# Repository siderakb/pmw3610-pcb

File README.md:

# PMW3610 PCB

Breakout board for the [PixArt PMW3610DM-SUDU](https://www.pixart.com/products-detail/21/PMW3610DM-SUDU), a low-power laser mouse sensor. An alternative to the [PMW3360 PCB](https://github.com/siderakb/pmw3360-pcb) for low-power applications. Can be used to make a mouse or trackball.

✨ Features:

- Compatible with [ZMK](https://zmk.dev/) projects. [Demo video](https://youtu.be/nyLZ6U8h7f0?t=17)
- Operates at either 1.8V or 3.3V voltage levels.
- Supports both 2.54mm pin headers and 0.5mm-pitch FFC/FPC connectors.
- The optical center of the sensor is located in the center of the PCB.

## PCB

Online preview available [here](https://kicanvas.org/?github=https%3A%2F%2Fgithub.com%2Fsiderakb%2Fpmw3610-pcb), powered by [KiCanvas](https://github.com/theacodes/kicanvas).

## Docs

📖 For more detailed information, please refer to the [docs](https://siderakb.ziteh.dev/mouse-sensors/pmw3610/rev2/) ([alternative link](https://github.com/siderakb/siderakb-website/blob/starlight/main/src/content/docs/mouse-sensors/pmw3610/rev2.md)).

[Changelog](./CHANGELOG.md)

## License

- **Hardware**: Available under the [CERN-OHL-P v2](/LICENSE) permissive license.
- **Firmware**: Licensed under [Apache 2.0](https://spdx.org/licenses/Apache-2.0.html) as identified by the SPDX in each file.

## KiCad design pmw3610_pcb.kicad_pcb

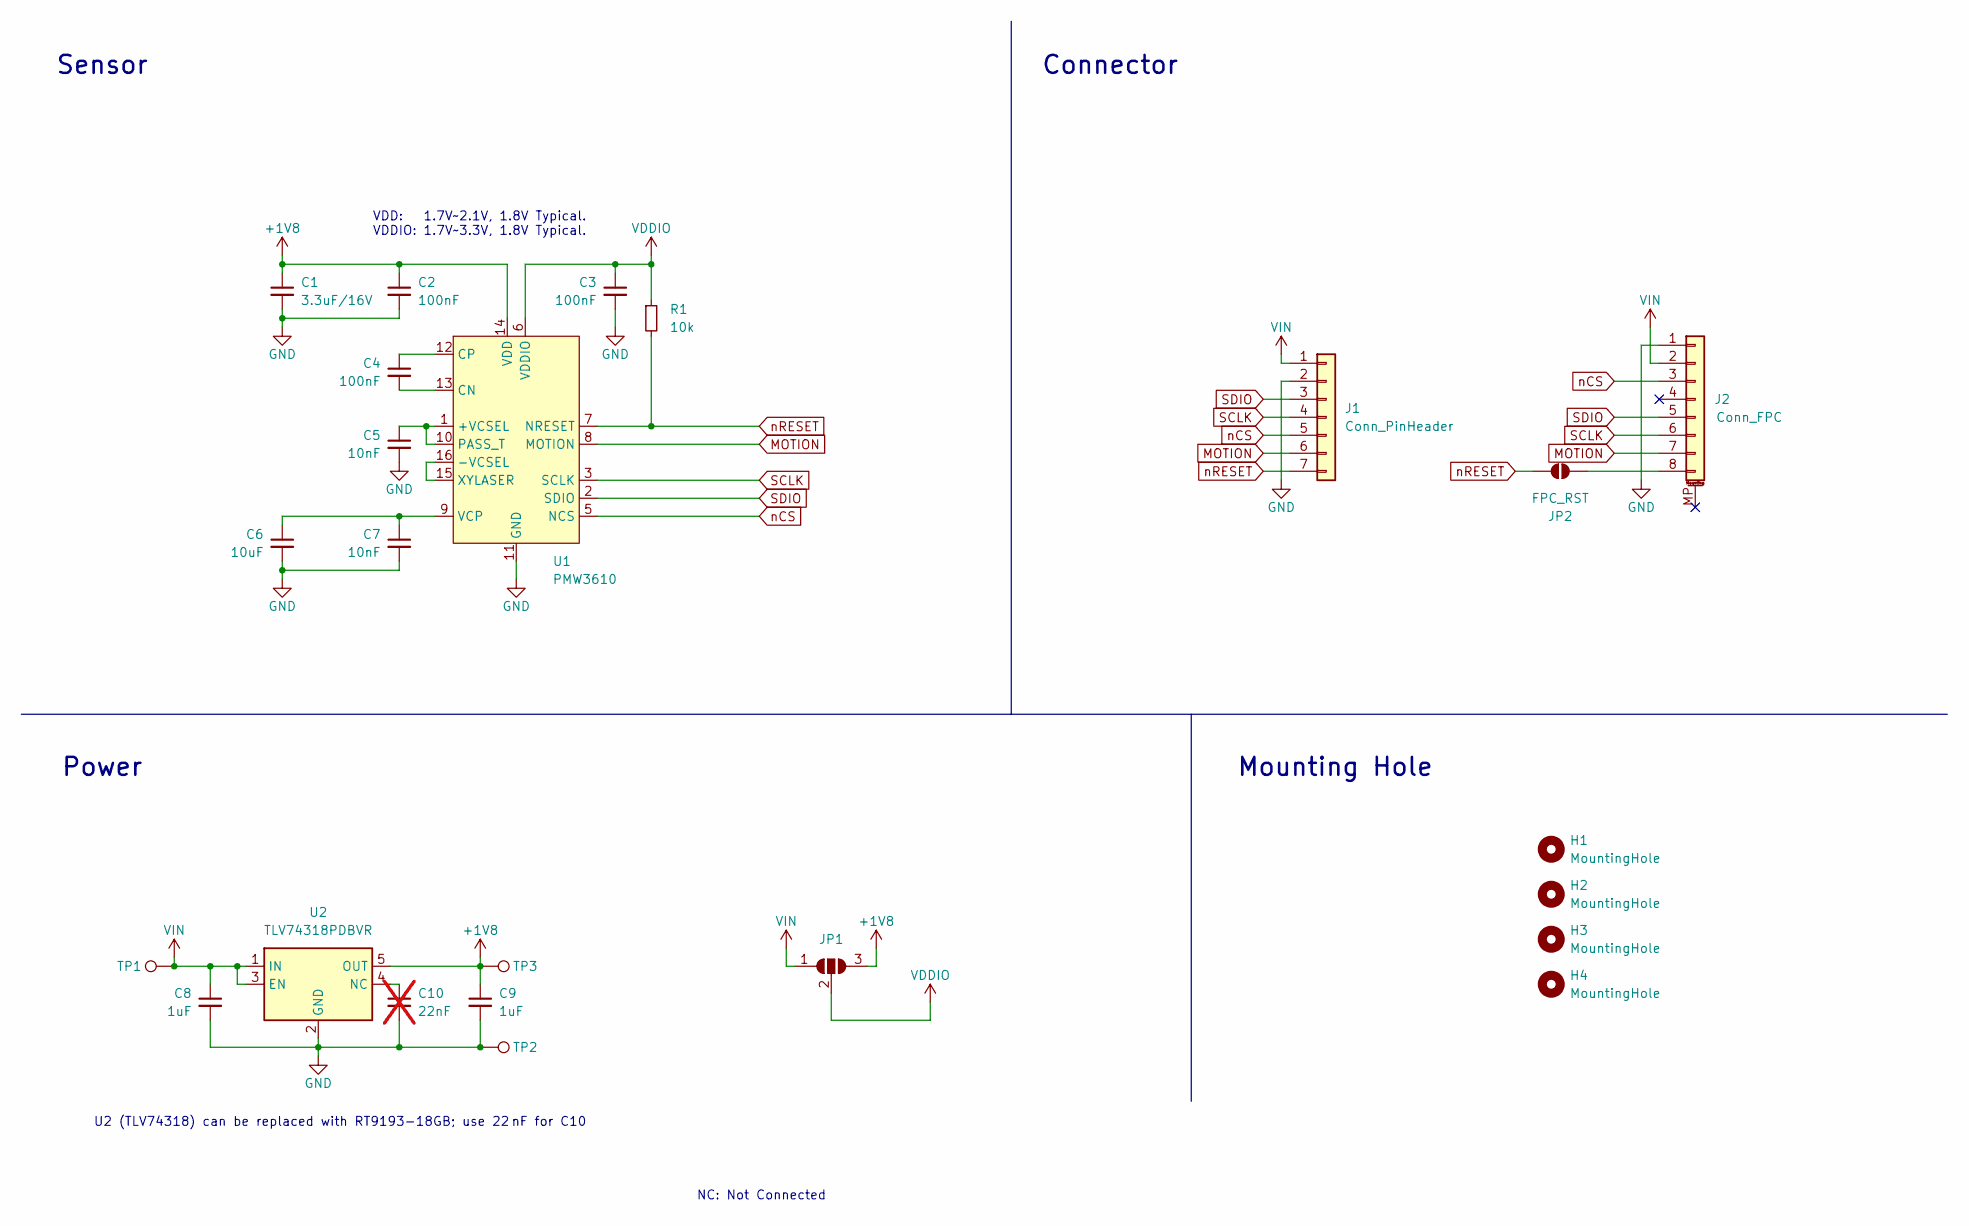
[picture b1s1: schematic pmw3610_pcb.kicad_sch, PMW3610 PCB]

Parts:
C1: 3.3uF/16V; C_0805_2012Metric; MFR. Part # TCC0805X7R335K250FT; JLCPCB Part # C7393948
C2, C3, C4: 100nF; C_0603_1608Metric; MFR. Part # CC0603KRX7R9BB104; JLCPCB Part # C14663
C5, C7: 10nF; C_0603_1608Metric; MFR. Part # 0603B103K500NT; JLCPCB Part # C57112
C6: 10uF; C_0805_2012Metric; MFR. Part # CL21A106KAYNNNE; JLCPCB Part # C15850
C8, C9: 1uF; C_0603_1608Metric; MFR. Part # CL10A105KB8NNNC; JLCPCB Part # C15849
C10: 22nF; C_0603_1608Metric; MFR. Part # CL10B223KB8NNNC; JLCPCB Part # C21122; not fitted
H1, H2, H3, H4: MountingHole; MountingHole_3.2mm_M3_ISO14580
J1: Conn_PinHeader; PinHeader_1x07_P2.54mm_Vertical
J2: Conn_FPC; FPC_8P_0.5mm_AFC01-S08FCA-00; MFR. Part # AFC01-S08FCA-00; JLCPCB Part # C262657
JP1: SolderJumper_3_Open; SolderJumper-3_P1.3mm_Open_RoundedPad1.0x1.5mm_NumberLabels
JP2: FPC_RST; SolderJumper-2_P1.3mm_Open_RoundedPad1.0x1.5mm
R1: 10k; R_0603_1608Metric; MFR. Part # 0603WAF1002T5E; JLCPCB Part # C25804
TP1, TP2, TP3: TestPoint; TestPoint_Pad_D1.5mm
U1: PMW3610; PMW3610DM-SUDU 16Pin; MFR. Part # PMW3610DM-SUDU; JLCPCB Part # C42442560
U2: TLV74318PDBVR; SOT-23-5_HandSoldering; MFR. Part # TLV74318PDBVR; JLCPCB Part # C485152

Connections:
+1V8: C1.1, C2.1, C9.1, JP1.3 (B), TP3.1, U1.14 (VDD), U2.5 (OUT)
GND: C1.2, C2.2, C3.2, C5.2, C6.2, C7.2, C8.2, C9.2, C10.2, J1.2, J2.1, TP2.1, U1.11 (GND), U2.2 (GND)
MOTION: J1.6, J2.7, U1.8 (MOTION)
unnamed: J2.8, JP2.2 (B)
unnamed: C5.1, U1.1 (+VCSEL), U1.10 (PASS_T)
unnamed: U1.15 (XYLASER), U1.16 (-VCSEL)
unnamed: C4.2, U1.13 (CN)
unnamed: C4.1, U1.12 (CP)
unnamed: C6.1, C7.1, U1.9 (VCP)
unnamed: C10.1, U2.4 (NC)
SCLK: J1.4, J2.6, U1.3 (SCLK)
SDIO: J1.3, J2.5, U1.2 (SDIO)
VDDIO: C3.1, JP1.2 (C), R1.1, U1.6 (VDDIO)
VIN: C8.1, J1.1, J2.2, JP1.1 (A), TP1.1, U2.1 (IN), U2.3 (EN)
nCS: J1.5, J2.3, U1.5 (NCS)
nRESET: J1.7, JP2.1 (A), R1.2, U1.7 (NRESET)

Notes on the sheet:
U2 (TLV74318) can be replaced with RT9193-18GB; use 22 nF for C10
Sensor
Power
Mounting Hole
NC: Not Connected
Connector
VDD: 1.7V~2.1V, 1.8V Typical. VDDIO: 1.7V~3.3V, 1.8V Typical.

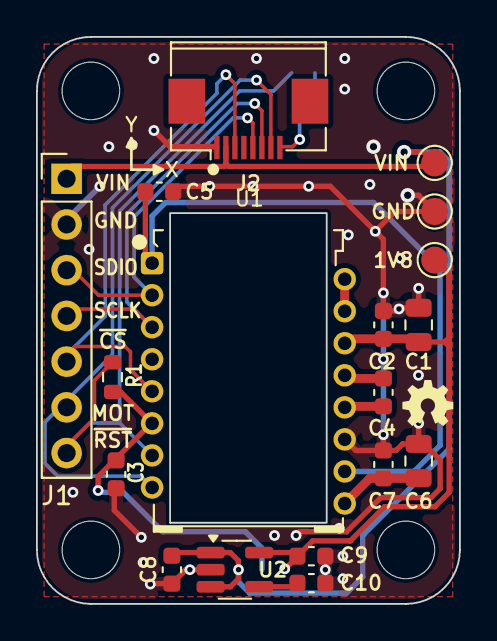
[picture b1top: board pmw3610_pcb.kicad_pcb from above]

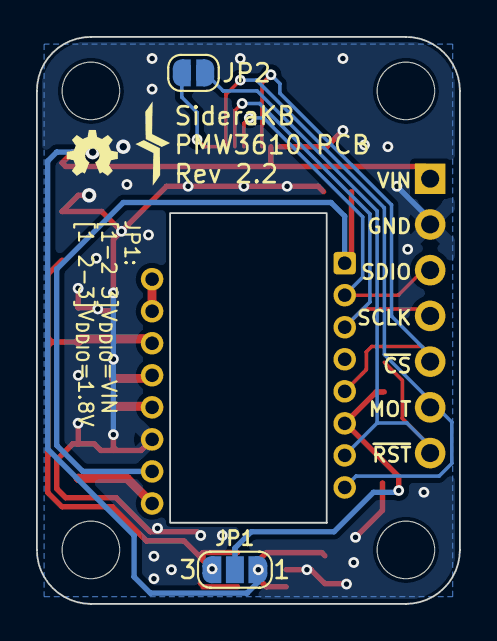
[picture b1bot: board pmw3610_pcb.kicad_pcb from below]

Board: 2 copper layers, 23.5 x 31.5 mm, 24 parts (6 on the bottom side), 16 nets.

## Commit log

2023-10-07 Init commit
2023-10-07 Add KiCad project files
2023-10-08 Add README.mc
2023-10-20 Add `J2` FPC/FFC connecter
2023-11-14 Create LICENSE
2025-04-17 chore: add `.gitattributes`
2025-07-17 feat: update PCB rev 1.1
2025-07-17 docs: update README
2025-07-17 docs: add CHANGELOG
2025-07-18 feat: update PMW3610 footprint
2025-07-18 docs: update CHANGELOG
2025-07-18 feat: increase the copper to board edge clearance to 0.4mm for better V-cut panelization
2025-07-20 feat: update FPC connector symbol
2025-07-22 feat: changed the J2 to the top layer
2025-07-22 feat: update part number of J2
2025-09-06 feat: add Zephyr NCS HID mouse project
2025-09-06 feat: enable RTT log
2025-09-07 feat: add PMW3610
2025-09-07 docs: update HID mouse firmware readme
2025-09-07 feat: add axis mark
2025-09-07 docs: update pixart pmw3610 device link
2025-09-07 docs: add axis direction deac
2025-09-07 docs: update image
2025-09-07 chore: remove .DS_Store files
2025-09-08 chore: update comment
2025-09-11 chore: update git config
2025-09-12 chore: update EOL config
2025-10-18 feat: add jumper JP2 for FFC/FPC and nRESET pin
2026-05-13 chore: ignore .history and KiCad project local settings
2026-05-13 feat: add top silkscreen header labels and reroute traces
    What this commit
    contains:
    - Adds readable top-side header labels for J1 for soldering.
    - Updates board/schematic revision to 2.2.
    - Reroutes traces and nearby items to fit the silkscreen labels.
    - Swaps TP1/TP2 placement intentionally for routing, with schematic and PCB matching.
2026-05-14 fix: correct assembly metadata and FPC footprint origin
    What this commit
    contains:
    - Excludes J1 from PCB assembly BOM/position outputs so JLC does not place the header.
    - Excludes C10 from BOM/position outputs while leaving it DNP.
    - Corrects the J2 FPC footprint origin so JLC placement previews correctly.
    - Updates the local FPC footprint library and placed footprint to match.

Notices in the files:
README.md:
License: CERN-OHL-P v2
pmw3610_pcb.kicad_pcb:
Open Source Hardware, CERN-OHL-P v2
